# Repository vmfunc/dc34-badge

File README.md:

# dc34 badge

my findings and custom stuff for the def con 34 badge.

it's a **baochip-1x**, bunnie's mostly-open 22nm soc. vexriscv rv32imac + mmu at 350mhz,
quad picorv32 "bio" coprocessor at 700mhz, 2mib ecc sram, 4mib rram, usb 2.0 hs, running
xous. enumerates as `1d50:6198` "baosec-lite".

first dc badge whose rtl you can actually read, which changes the job. reversing something
you could have read is self-inflicted here.

## the ctf

flag 1 is stated outright in `bao1x-api/src/offsets/baosec.rs:151`:

```rust
/// A test value placed by FT into the memory array. If you can read the original value,
/// you've captured a flag!
/// There is a second flag stored somewhere else. Can you find it?
pub const THE_FLAG_1: SlotIndex = SlotIndex::Data(260, PartitionAccess::Fw0, RwPerms::ReadWrite);
```

32 bytes at `0x603E_2080`, burned at final test, `Fw0` so only boot1 and the keystore touch
it. not derived from anything, so it can't be computed. only read.

and it's in `KEY_SLOTS`, the set boot1 wipes on entry to developer mode. `sigcheck.rs:735`
runs `erase_secrets()` *before* unsigned code executes, so the erase is a precondition of
running your own image, not a consequence. no window, no ordering trick. flashing the badge
isn't a risk to the flag, it's the destruction of it.

that's the whole design, and it's a good one.

## every software path, and what killed it

measured on hardware, not inferred.

| path | why it's dead |
| --- | --- |
| bio bdma read | whitelist entirely empty. a filtered read gets redirected to `gutter` (resets to 0), nothing answers there, the core hangs. the hang is the oracle |
| boot1 `peek` | refuses `0x603D_A000`..`0x6040_0000` by address, *and* it's behind `unsafe-debug` and not in the shipped build |
| boot1 `uf2` | write path, bounded below `0x603D_A000`, can't address the flag, and unsigned use triggers the erase anyway |
| `image` verb | bounded 2048-byte framebuffer, 32 chunks, sequence enforced. the u16 index is not an oob write |
| ctaphid | init-only stub. init allocates channels and advertises caps `0x05`, then ping/wink/msg/cbor all return nothing |
| jtag | fused off, checked against `secboot.rs`'s hardcoded ifr reference at `0x6040_0180` |
| sign our own image | only `bao1`/`bao2`/`beta` avoid the erase, none of those private keys are public |

bio code execution *does* work. `bio` is an undocumented console verb that turns out to be
`baochip/bio-loader`'s protocol. proved it by loading a program that pushes `0x0BADF00D`,
then one that pops-adds-one-pushes, and reading back `badf00e`. it just can't reach memory.

so flag 1 is physical, and bunnie says so himself in the comment right above it: the
nuisance keys exist "to annoy microscopists trying to read the secret key by directly
imaging the rram array", and he concedes any readout above 97% accuracy gets repaired by
ecc. he named the attack, the tool and the pass mark. it's an iris job.

i gave up flag 1 on this badge on purpose, no microscope on hand, and flashed my own
firmware instead. slot 260 is erased here. for an unflashed badge the answer is still iris.

## the bug worth reporting

`rrc.sv:392-395` derives the acram index differently on its two paths. writes use
`{haddr[13:5], acram_idx}`, granular to 32 bytes. reads use `haddr[16:6]`, granular to 64.
a data slot is 32 bytes, so the read path drops the bit separating a slot from its
neighbour and the acl read index collapses to `slot >> 1`.

| pair | slots | access |
| --- | --- | --- |
| 130 | `THE_FLAG_1` (260) / `COLLATERAL[0]` (261) | fw0 / fw0 |
| **132** | **`COLLATERAL[3]` (264) / `BOOT1_PK_RECEIPT_SLOT0` (265)** | **fw0 / open** |

pair 132 straddles a privilege boundary. if the permissive side wins, slot 264 is readable
from a context that should never see it. arithmetic, checkable, worth telling baochip
regardless of the ctf. details in [notes/acl-aliasing.md](notes/acl-aliasing.md).

also a plain overflow in `test hue`: `base + 32` on a `u8` wraps, so asking for deep magenta
silently hands you green. fixed in my build.

## flag 2

still open, and it's the interesting one. from `vendor/dc34-vault/README.md`: light patterns
are traded between badges by qr and encrypted with a key **shared across the entire
population**. extract it and you're a seeder for arbitrary patterns. no microscope needed.
ranked leads and kill tests in [notes/leads.md](notes/leads.md).

## my firmware

reproduces bunnie's build, `loader.uf2` and `swap.uf2` byte-identical in size to the
official release, `xous.uf2` bigger by exactly what i added. deviations:

- `dc34-console` with `--features qa-test --features misc-test`. there are five feature
  gates in `cmds/test.rs`, not one, and `hue` is behind the second. `misc-test` carries
  `hue`/`autogamy`/`qrshow`/`qrget`/`cam`/`accel`/`adc`, `qa-test` carries
  `rate`/`transmute`/`bt`/`mate`. left `owc-test` and `wfi-stress-test` off, the first
  spends finite one-way counters and the second can hang the badge
- idle screen is mine: pfp, `vmfunc`, `it/its`. dc logo gone. regenerate with
  `tools/make_badge_art.py`
- strip reads `ud2.rip`
- boots lavender and breathing, nothing to type
- `test hue <val> [width]`, width 0 for one flat colour

on the breathing: the bio renderer computes brightness as
`cos(cd_period * 2pi * i/(count-1) +/- indextime/tau(cd_rate) * 2pi)`. `cd_period = 0` puts
every led in phase so the strip rises and falls together. `cd_rate` maps 0..255 onto tau
60..700, high is slow. that's the whole effect, no new code.

the default uses `force()` instead of setting the gene, so the heritable gene survives and
qr trading still works. it holds through repaints until you run `test hue`, trade, or breed,
then hands over for good.

## layout

```
notes/          the thinking. 00-log is the spine, leads.md is the hypothesis queue
firmware/       dumps/ is the vendor's signed release, built/ is mine, MANIFEST.md hashes both
vendor/         the six official bunnie repos, pinned, with provenance
tools/          host side, all of it safe to run half asleep
re/             ghidra scripts, bio programs, strings
art/            the ud2 wordmark and the generated badge card
captures/       gitignored. big, and worth exactly as much as the notes taken off them
solves/         one dir per challenge
docs/           the writeup
```

images get committed, captures don't. a firmware image is small evidence worth having in
history so a later diff can prove what changed. a logic capture is hundreds of mb of
observation. no git-lfs, it wants a network round trip and the whole premise is the network
won't be there.

## toolchain

```
nix develop
```

pinned flake, evaluates on x86_64-linux and aarch64-darwin. rv32 cross toolchain, ghidra,
radare2, binwalk, openocd, probe-rs, picotool, esptool, picocom, sigrok, rtl-sdr, hackrf,
python with pwntools/capstone/keystone/unicorn. rf gui tools are linux-only in nixpkgs and
gated accordingly.

pre-warm before you lose network:

```
nix develop --profile ./.dc34-profile -c true
```

## tools

```
./tools/console.py "help" "ver"                   talk to the console, refuses the fatal verbs
./tools/bio_upload.py --asm re/scripts/x.S        assemble + upload a bio program
./tools/sweep.py --range 0x603E0000 0x603F0000    map what bio may read
./tools/oled.py --ascii art/ud2.txt               picture onto the panel
./tools/leds.py --palette rose-pine               colours through the running lightgene
./tools/ctap.py info                              ctaphid
./tools/boot1.py                                  drive the bootloader, read-only
./tools/flash.sh firmware/built                   flash. makes you type FLASH
./tools/make_badge_art.py --pfp x.jpg             regenerate the idle screen
```

three things that cost me real time:

**console is 1000000 baud**, not 115200. wrong baud is indistinguishable from no console.

**pace writes inside the line.** console input goes through the keyboard service and its
buffer overflows on a fast full-length line, then takes the whole console silent. but
byte-at-a-time is worse: each tiny write becomes its own usb packet and the firmware
mis-samples it, so `ver` echoes back as `vrr`. corrupted input that still parses wastes far
more time than input that's loudly dropped. 24-byte pieces.

**`bio tx` is not a host-to-core path.** it feeds the queue the core pushes *to*, so anything
you send comes straight back on `bio rx` without a core ever seeing it. bake what a program
needs into the program. and a value pushed once gets eaten by the badge's own lightgenes
loop, so only continuous pushing survives.

## building the firmware

needs `xous-core` as a **sibling** dir, on **`dev`**, not the rev `dc34-console` pins.
`dc34-console` wants `keystore/owc-inc` which only exists on dev. tag the checkout or the
signer dies with `SemVer::from_git: no major version`.

```
cargo xtask install-toolkit          # prebuilt riscv32imac-unknown-xous std, no build-std
cargo xtask baosec-lite \
  ../dc34-console/target/riscv32imac-unknown-xous-elf/release/dc34-console~flash \
  ../dc34-vault/target/riscv32imac-unknown-xous-elf/release/dc34-vault \
  --no-timestamp --feature usb --kernel-feature debug-proc --no-verify
```

cratespec syntax matters: bare name is a workspace crate, `name^ver` is crates.io,
`name#url` is prebuilt, anything with a `/` is a prebuilt elf on disk, and
`name~swap|flash|ram` pins the region. out-of-tree apps go in as built binaries without
joining the xous workspace.

flash: hold `PROG` while plugging in, `./tools/flash.sh <dir>`, press `PROG` again.
back to stock: `./tools/flash.sh firmware/dumps/dc34-badge-latest`.

## links

- badge: https://defcon.org/34b/
- bunnie on the soc: https://www.bunniestudios.com/blog/2026/baochip-1x-a-mostly-open-22nm-soc-for-high-assurance-applications/
- sources: https://github.com/bunnie (dc34-console, dc34-vault, dc34-api, dc34-image, dc34-bio)
- rtl: https://github.com/baochip/baochip-1x
- xous: https://github.com/betrusted-io/xous-core
- iris: https://bunnie.org/iris

---

not affiliated with the badge designers. `vendor/` is their code, vendored with provenance in
`vendor/README.md`. `dc34-console`, `dc34-vault` and `dc34-api` ship no licence file, so
that's public-but-unlicensed, worth an email to `dc34@baochip.com` before anyone builds on
this.

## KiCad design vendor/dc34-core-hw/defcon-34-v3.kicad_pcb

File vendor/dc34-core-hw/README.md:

# DEFCON 34 Core Module Hardware Files

This contains the KiCAD files for the core module hardware design.

See [defcon's support page](https://defcon.org/34b) for more details.

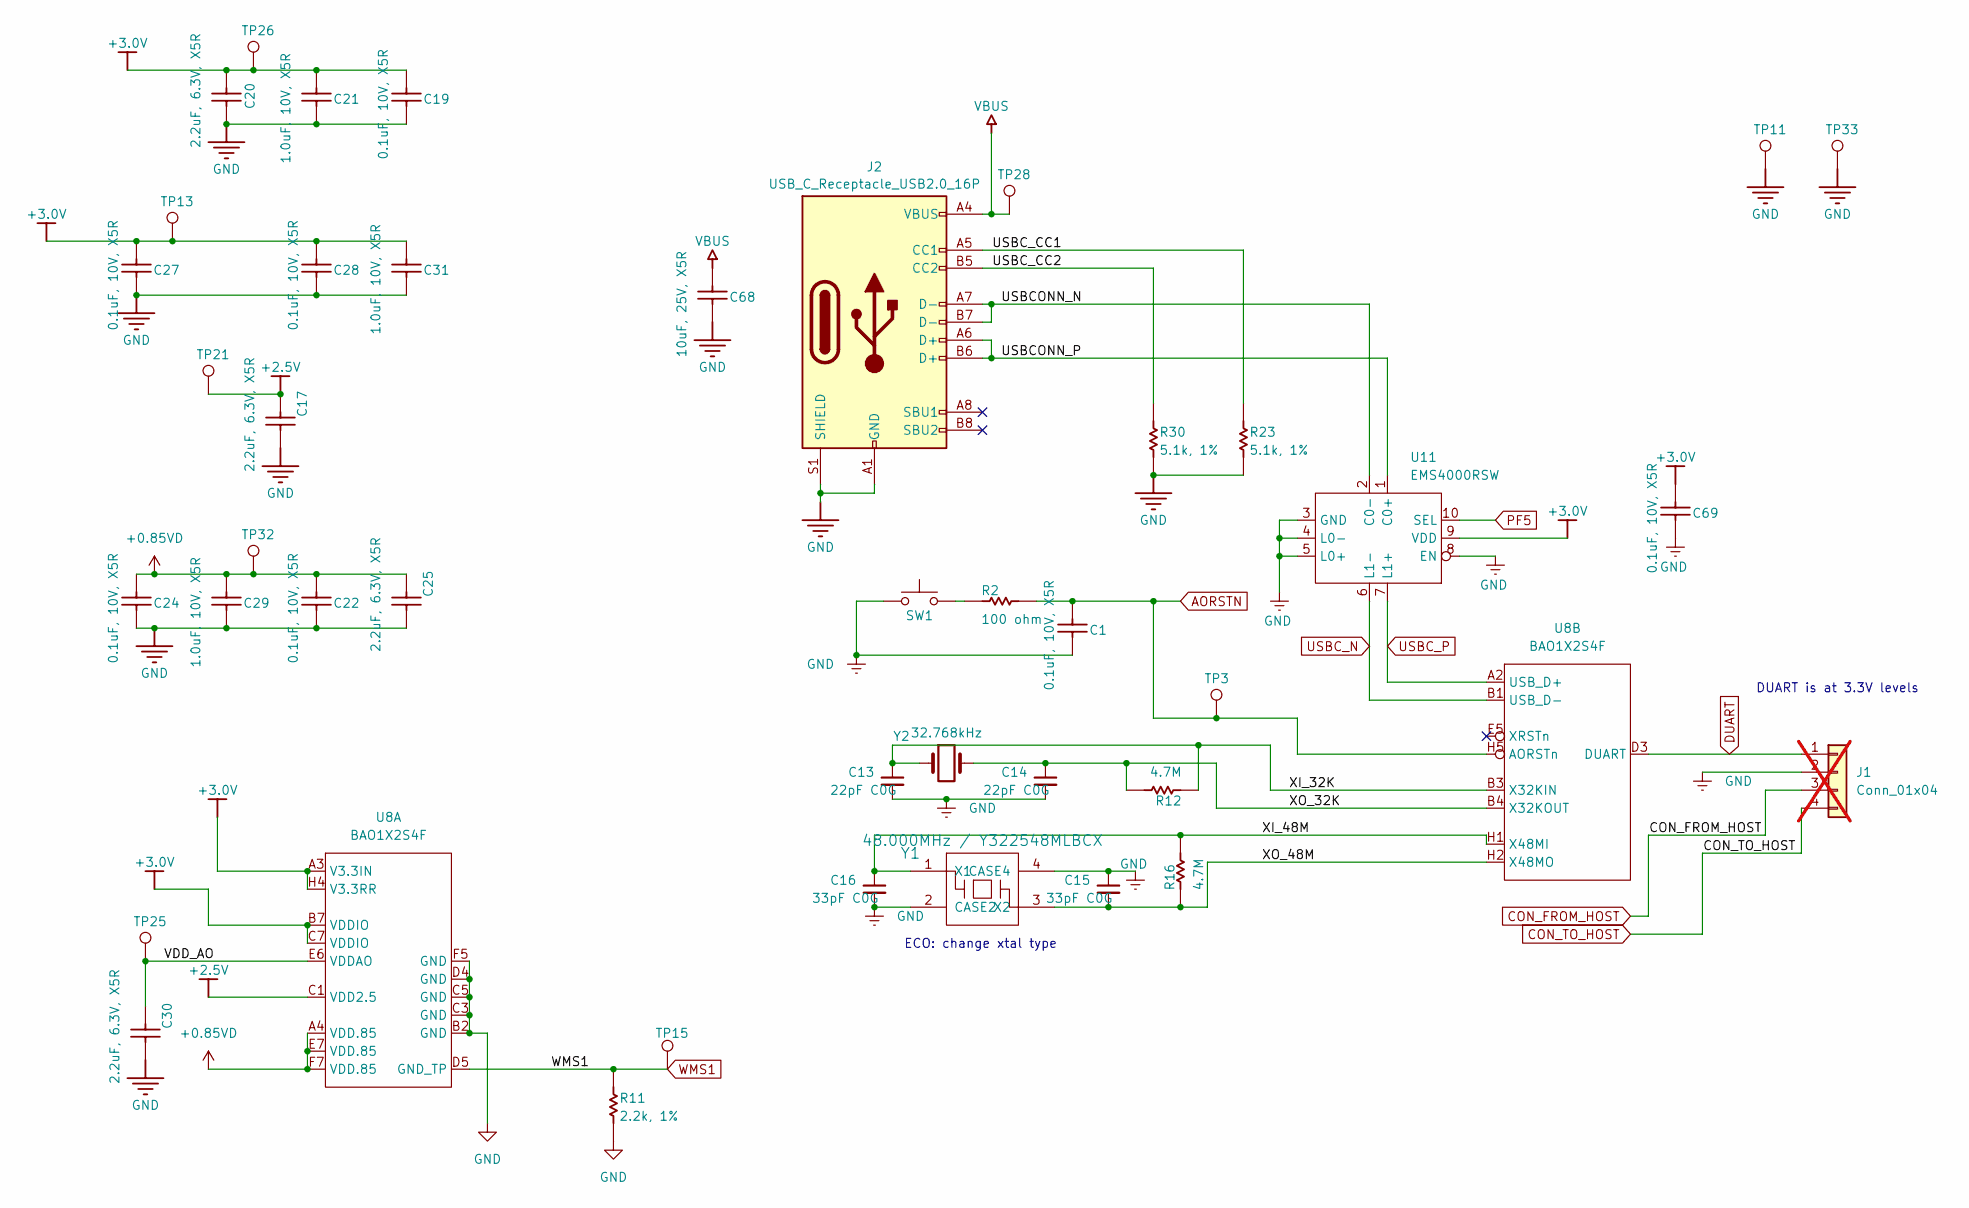
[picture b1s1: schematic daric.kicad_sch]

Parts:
C1, C19, C22, C24, C27, C28, C69: 0.1uF, 10V, X5R; C_0201_0603Metric; MPN CL05B104KO5NNNC; LCSC C76934
C13, C14: 22pF C0G; C_0201_0603Metric; Rating C0G 50V 0201; MPN ANY; LCSC C57783
C15, C16: 33pF C0G; C_0201_0603Metric; Rating C0G 50V 0201; MPN ANY; LCSC C56903
C17, C20, C25, C30: 2.2uF, 6.3V, X5R; C_0201_0603Metric; MPN GRM033R60J225ME47D; LCSC C76933
C21, C29, C31: 1.0uF, 10V, X5R; C_0201_0603Metric; MPN CL05A105KA5NQNC; LCSC C76935
C68: 10uF, 25V, X5R; C_0603_1608Metric; MPN CL10A106MA8NRNC; LCSC C96446
J1: Conn_01x04; PinHeader_1x04_P2.54mm_Vertical; not fitted
J2: USB_C_Receptacle_USB2.0_16P; USB_C_Receptacle_HRO_TYPE-C-31-M-12; LCSC C165948
R2: 100 ohm; R_0402_1005Metric; MPN ANY; LCSC C106232
R11: 2.2k, 1%; R_0402_1005Metric; MPN ANY; LCSC C114762
R12, R16: 4.7M; R_0402_1005Metric; MPN ANY; LCSC C474132
R23, R30: 5.1k, 1%; R_0402_1005Metric; MPN ANY; LCSC C25905
SW1: SW_Push; TS24CA; MPN TS24CA; LCSC C393942
TP3, TP11, TP13, TP15, TP21, TP25, TP26, TP28, TP32, TP33: TestPoint; TestPoint_Pad_D1.2mm
U8: BAO1X2S4F; WLCSP-71_9x8_4.062x3.762mm
U11: EMS4000RSW; QFN-10_1.4x1.8_Pitch0.4mm; LCSC C49186227
Y1: 48.000MHz / Y322548MLBCX; Crystal_SMD_3225-4Pin_3.2x2.5mm; LCSC C49158137
Y2: 32.768kHz; Crystal_SMD_TXC_9HT11-2Pin_2.0x1.2mm; LCSC C55208

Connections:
+0.85VD: C22.1, C24.1, C25.1, C29.1, TP32.1, U8.A4 (VDD.85), U8.E7 (VDD.85), U8.F7 (VDD.85); also elsewhere on the board
+2.5V: C17.1, TP21.1, U8.C1 (VDD2.5)
+3.0V: C19.1, C20.1, C21.1, C27.1, C28.1, C31.1, C69.1, TP13.1, TP26.1, U8.A3 (V3.3IN), U8.B7 (VDDIO), U8.C7 (VDDIO), U8.H4 (V3.3RR), U11.9 (VDD); also elsewhere on the board
/Daric/USBCONN_N: J2.A7 (D-), J2.B7 (D-), U11.2 (C0-)
/Daric/USBCONN_P: J2.A6 (D+), J2.B6 (D+), U11.1 (C0+)
/Daric/USBC_CC1: J2.A5 (CC1), R23.2
/Daric/USBC_CC2: J2.B5 (CC2), R30.2
/Daric/VDD_AO: C30.1, TP25.1, U8.E6 (VDDAO)
/Daric/XI_32K: C13.1, R12.1, U8.B3 (X32KIN), Y2.1
/Daric/XI_48M: C16.1, R16.2, U8.H1 (X48MI), Y1.1 (X1)
/Daric/XO_32K: C14.1, R12.2, U8.B4 (X32KOUT), Y2.2
/Daric/XO_48M: C15.2, R16.1, U8.H2 (X48MO), Y1.3 (X2)
AORSTN: C1.1, R2.2, TP3.1, U8.H5 (AORSTn); also elsewhere on the board
CON_FROM_HOST: J1.3; also elsewhere on the board
CON_TO_HOST: J1.4; also elsewhere on the board
DUART: J1.1, U8.D3 (DUART); also elsewhere on the board
GND: C1.2, C13.2, C14.2, C15.1, C16.2, C17.2, C19.2, C20.2, C21.2, C22.2, C24.2, C25.2, C27.2, C28.2, C29.2, C30.2, C31.2, C68.2, C69.2, J1.2, J2.A1 (GND), J2.A12 (GND), J2.B1 (GND), J2.B12 (GND), J2.S1 (SHIELD), R11.2, R23.1, R30.1, SW1.1, TP11.1, TP33.1, U8.B2 (GND), U8.C3 (GND), U8.C5 (GND), U8.D4 (GND), U8.F5 (GND), U11.3 (GND), U11.4 (L0-), U11.5 (L0+), U11.8 (EN), Y1.2 (CASE2), Y1.4 (CASE4); also elsewhere on the board
unnamed: R2.1, SW1.2
PF5: U11.10 (SEL); also elsewhere on the board
USBC_N: U8.B1 (USB_D-), U11.6 (L1-)
USBC_P: U8.A2 (USB_D+), U11.7 (L1+)
VBUS: C68.1, J2.A4 (VBUS), J2.A9 (VBUS), J2.B4 (VBUS), J2.B9 (VBUS), TP28.1; also elsewhere on the board
WMS1: R11.1, TP15.1, U8.D5 (GND_TP); also elsewhere on the board

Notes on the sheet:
ECO: change xtal type
DUART is at 3.3V levels

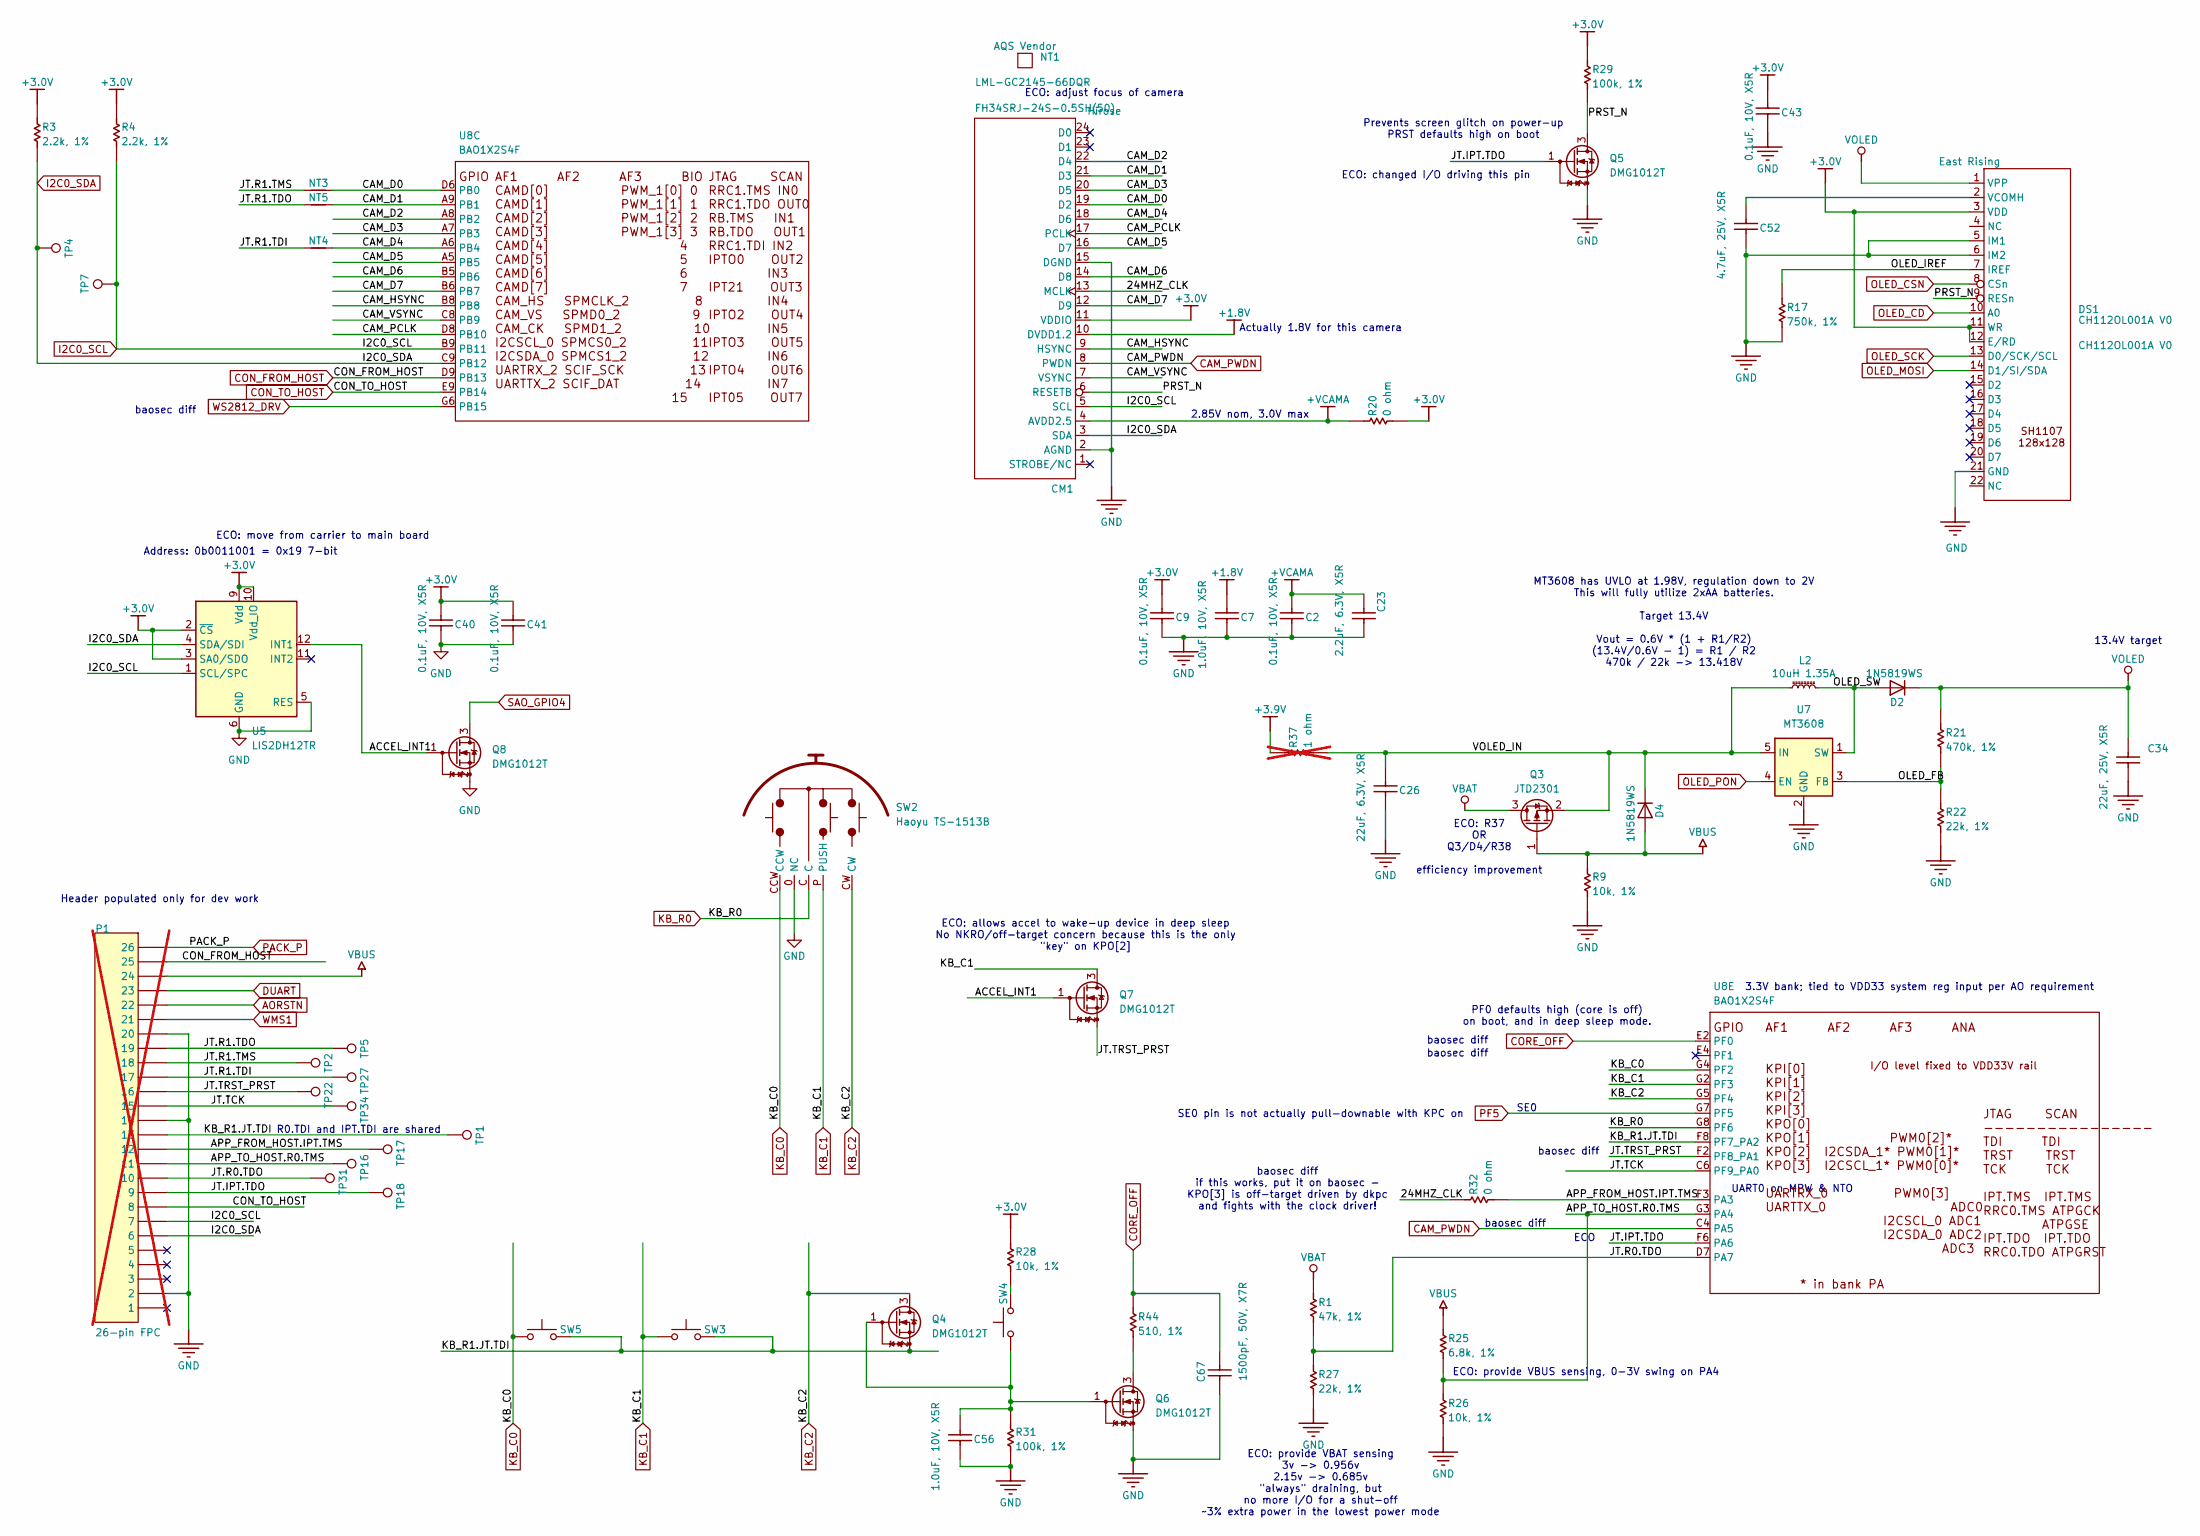
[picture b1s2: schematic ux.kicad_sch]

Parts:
C2, C9, C40, C41, C43: 0.1uF, 10V, X5R; C_0201_0603Metric; MPN CL05B104KO5NNNC; LCSC C76934
C7, C56: 1.0uF, 10V, X5R; C_0201_0603Metric; MPN CL05A105KA5NQNC; LCSC C76935
C23: 2.2uF, 6.3V, X5R; C_0201_0603Metric; MPN GRM033R60J225ME47D; LCSC C76933
C26: 22uF, 6.3V, X5R; C_0603_1608Metric; MPN CL10A226MQ8NRNC; LCSC C59461
C34: 22uF, 25V, X5R; C_0805_2012Metric; LCSC C7419435
C52: 4.7uF, 25V, X5R; C_0805_2012Metric; MPN CL21A475KAQNNNE; LCSC C1779
C67: 1500pF, 50V, X7R; C_0402_1005Metric; MPN CC0402KRX7R9BB152; LCSC C107022
CM1: HRS_FH34SRJ-24S-0.5SH(50); MPN FH34SRJ-24S-0.5SH(50); LCSC C324726
D2, D4: 1N5819WS; D_SOD-323-B; MPN SD103AWS; LCSC C191023
DS1: CH112OL001A V0; ER-OLED-1.12_BACKSIDE-1.5mm-offset; MPN CH112OL001A V0
L2: 10uH 1.35A; L_APV_ANR252012; MPN FHD252012S-100MT; LCSC C602018
NT1: LML-GC2145-66DQR; GC2145-lens-up; PARTNUMBER LML-GC2145-66DQR
NT3, NT4, NT5: NetTie_2; NetTie-2_SMD_Pad0.5mm
P1: 26-pin FPC; HRS_FH34SRJ-26S-0.5SH(50); MPN FH34SRJ-26S-0.5SH(99); LCSC C596726; not fitted
Q3: JTD2301; SOT-23; LCSC C42443454
Q4, Q5, Q6, Q7, Q8: DMG1012T; SOT-523-B; LCSC C20512
R1: 47k, 1%; R_0201_0603Metric; MPN ANY; LCSC C138139
R3, R4: 2.2k, 1%; R_0402_1005Metric; MPN ANY; LCSC C114762
R9, R26, R28: 10k, 1%; R_0201_0603Metric; MPN ANY; LCSC C106225
R17: 750k, 1%; R_0402_1005Metric; MPN ANY; LCSC C2909381
R20, R32: 0 ohm; R_0402_1005Metric; MPN ANY; LCSC C17168
R21: 470k, 1%; R_0402_1005Metric; MPN ANY; LCSC C25790
R22, R27: 22k, 1%; R_0201_0603Metric; MPN ANY; LCSC C474416
R25: 6.8k, 1%; R_0201_0603Metric; MPN ANY; LCSC C274877
R29, R31: 100k, 1%; R_0201_0603Metric; MPN ANY; LCSC C106224
R37: 1 ohm; R_0402_1005Metric; MPN ANY; LCSC C185446; not fitted
R44: 510, 1%; R_0201_0603Metric; MPN ANY; LCSC C965358
SW2: Haoyu TS-1513B; TS-1513B; LCSC C318951
SW3, SW4, SW5: SW_Push; SW_Push_1P1T_XKB_TS-1187A; MPN TS-1187A-B-B-B; LCSC C528026
TP1, TP2, TP4, TP5, TP7, TP16, TP17, TP18, TP22, TP27, TP31, TP34: TestPoint; TestPoint_Pad_D1.2mm
U5: LIS2DH12TR; LGA-12_2x2mm_P0.5mm; LCSC C110926
U7: MT3608; SOT-23-6; LCSC C84817
U8: BAO1X2S4F; WLCSP-71_9x8_4.062x3.762mm

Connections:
+1.8V: C7.1, CM1.10 (DVDD1.2); also elsewhere on the board
+3.0V: C9.1, C40.1, C41.1, C43.1, CM1.11 (VDDIO), DS1.3 (VDD), DS1.11 (WR), DS1.12 (E/RD), R3.1, R4.1, R20.2, R28.1, R29.1, U5.2 (~CS), U5.3 (SA0/SDO), U5.9 (Vdd), U5.10 (Vdd_IO); also elsewhere on the board
+3.9V: R37.1; also elsewhere on the board
+VCAMA: C2.1, C23.1, CM1.4 (AVDD2.5), R20.1
/ux/24MHZ_CLK: CM1.13 (MCLK), R32.1
/ux/ACCEL_INT1: Q7.1 (G), Q8.1 (G), U5.12 (INT1)
/ux/APP_FROM_HOST.IPT.TMS: P1.12, R32.2, TP17.1, U8.F3 (PA3)
/ux/APP_TO_HOST.R0.TMS: P1.11, R25.2, R26.1, TP16.1, U8.G3 (PA4)
/ux/CAM_D0: CM1.19 (D2), NT3.2, U8.D6 (PB0)
/ux/CAM_D1: CM1.21 (D3), NT5.2, U8.A9 (PB1)
/ux/CAM_D2: CM1.22 (D4), U8.A8 (PB2)
/ux/CAM_D3: CM1.20 (D5), U8.A7 (PB3)
/ux/CAM_D4: CM1.18 (D6), NT4.2, U8.A6 (PB4)
/ux/CAM_D5: CM1.16 (D7), U8.A5 (PB5)
/ux/CAM_D6: CM1.14 (D8), U8.B5 (PB6)
/ux/CAM_D7: CM1.12 (D9), U8.B6 (PB7)
/ux/CAM_HSYNC: CM1.9 (HSYNC), U8.B8
/ux/CAM_PCLK: CM1.17 (PCLK), U8.D8 (PB10)
/ux/CAM_VSYNC: CM1.7 (VSYNC), U8.C8 (PB9)
/ux/JT.IPT.TDO: P1.9, Q5.1 (G), TP18.1, U8.F6 (PA6)
/ux/JT.R0.TDO: P1.10, R1.2, R27.1, TP31.1, U8.D7 (PA7)
/ux/JT.R1.TDI: NT4.1, P1.17, TP27.1
/ux/JT.R1.TDO: NT5.1, P1.19, TP5.1
/ux/JT.R1.TMS: NT3.1, P1.18, TP2.1
/ux/JT.TCK: P1.15, TP34.1, U8.C6 (PF9_PA0)
/ux/JT.TRST_PRST: P1.16, Q7.2 (S), TP22.1, U8.F2 (PF8_PA1)
/ux/KB_R1.JT.TDI: P1.13, Q4.2 (S), SW3.2, SW5.2, TP1.1, U8.F8 (PF7_PA2)
/ux/OLED_FB: R21.2, R22.1, U7.3 (FB)
/ux/OLED_IREF: DS1.7 (IREF), R17.1
/ux/OLED_SW: D2.2 (A), L2.2, U7.1 (SW)
/ux/PRST_N: CM1.6 (RESETB), DS1.9 (RESn), Q5.3 (D), R29.2
/ux/VOLED_IN: C26.1, D4.1 (K), L2.1, Q3.2 (S), R37.2, U7.5 (IN)
AORSTN: P1.22; also elsewhere on the board
CAM_PWDN: CM1.8 (PWDN), U8.C4 (PA5)
CON_FROM_HOST: P1.25, U8.D9 (PB13); also elsewhere on the board
CON_TO_HOST: P1.8, U8.E9 (PB14); also elsewhere on the board
CORE_OFF: C67.2, R44.1, U8.E2 (PF0); also elsewhere on the board
DUART: P1.23; also elsewhere on the board
GND: C2.2, C7.2, C9.2, C23.2, C26.2, C34.2, C40.2, C41.2, C43.2, C52.2, C56.2, C67.1, CM1.2 (AGND), CM1.15 (DGND), DS1.5 (IM1), DS1.6 (IM2), DS1.21 (GND), P1.2, P1.14, P1.20, Q5.2 (S), Q6.2 (S), Q8.2 (S), R9.2, R17.2, R22.2, R26.2, R27.2, R31.2, SW2.0 (NC), U5.5 (RES), U5.6 (GND), U5.7 (GND), U5.8 (GND), U7.2 (GND); also elsewhere on the board
I2C0_SCL: CM1.5 (SCL), P1.7, R4.2, TP7.1, U5.1 (SCL/SPC), U8.B9 (PB11); also elsewhere on the board
I2C0_SDA: CM1.3 (SDA), P1.6, R3.2, TP4.1, U5.4 (SDA/SDI), U8.C9 (PB12); also elsewhere on the board
KB_C0: SW2.CCW, SW5.1, U8.G4 (PF2)
KB_C1: Q7.3 (D), SW2.P (PUSH), SW3.1, U8.G2 (PF3)
KB_C2: Q4.3 (D), SW2.CW, U8.G5 (PF4)
KB_R0: SW2.C, U8.G8 (PF6)
unnamed: C52.1, DS1.2 (VCOMH)
unnamed: C56.1, Q4.1 (G), Q6.1 (G), R31.1, SW4.1
unnamed: Q6.3 (D), R44.2
unnamed: R28.2, SW4.2
OLED_CD: DS1.10 (A0); also elsewhere on the board
OLED_CSN: DS1.8 (CSn); also elsewhere on the board
OLED_MOSI: DS1.14 (D1/SI/SDA); also elsewhere on the board
OLED_PON: U7.4 (EN); also elsewhere on the board
OLED_SCK: DS1.13 (D0/SCK/SCL); also elsewhere on the board
PACK_P: P1.26; also elsewhere on the board
PF5: U8.G7 (PF5); also elsewhere on the board
SAO_GPIO4: Q8.3 (D); also elsewhere on the board
VBAT: Q3.3 (D), R1.1; also elsewhere on the board
VBUS: D4.2 (A), P1.24, Q3.1 (G), R9.1, R25.1; also elsewhere on the board
VOLED: C34.1, D2.1 (K), DS1.1 (VPP), R21.1
WMS1: P1.21; also elsewhere on the board
WS2812_DRV: U8.G6 (PB15); also elsewhere on the board

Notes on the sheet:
Prevents screen glitch on power-up PRST defaults high on boot
Header populated only for dev work
ECO: changed I/O driving this pin
3.3V bank; tied to VDD33 system reg input per AO requirement
PF0 defaults high (core is off) on boot, and in deep sleep mode.
SE0 pin is not actually pull-downable with KPC on
SE0
ECO
ECO: provide VBUS sensing, 0-3V swing on PA4
baosec diff
UART0 on MPW & NTO
baosec diff if this works, put it on baosec - KPO[3] is off-target driven by dkpc and fights with the clock driver!
Actually 1.8V for this camera
MT3608 has UVLO at 1.98V, regulation down to 2V This will fully utilize 2xAA batteries. Target 13.4V Vout = 0.6V * (1 + R1/R2) (13.4V/0.6V - 1) = R1 / R2 470k / 22k -> 13.418V
ECO: adjust focus of camera
13.4V target
ECO: move from carrier to main board
2.85V nom, 3.0V max
ECO: R37 OR Q3/D4/R38 efficiency improvement
ECO: provide VBAT sensing 3v -> 0.956v 2.15v -> 0.685v "always" draining, but no more I/O for a shut-off ~3% extra power in the lowest power mode
Address: 0b0011001 = 0x19 7-bit
R0.TDI and IPT.TDI are shared
ECO: allows accel to wake-up device in deep sleep No NKRO/off-target concern because this is the only "key" on KPO[2]

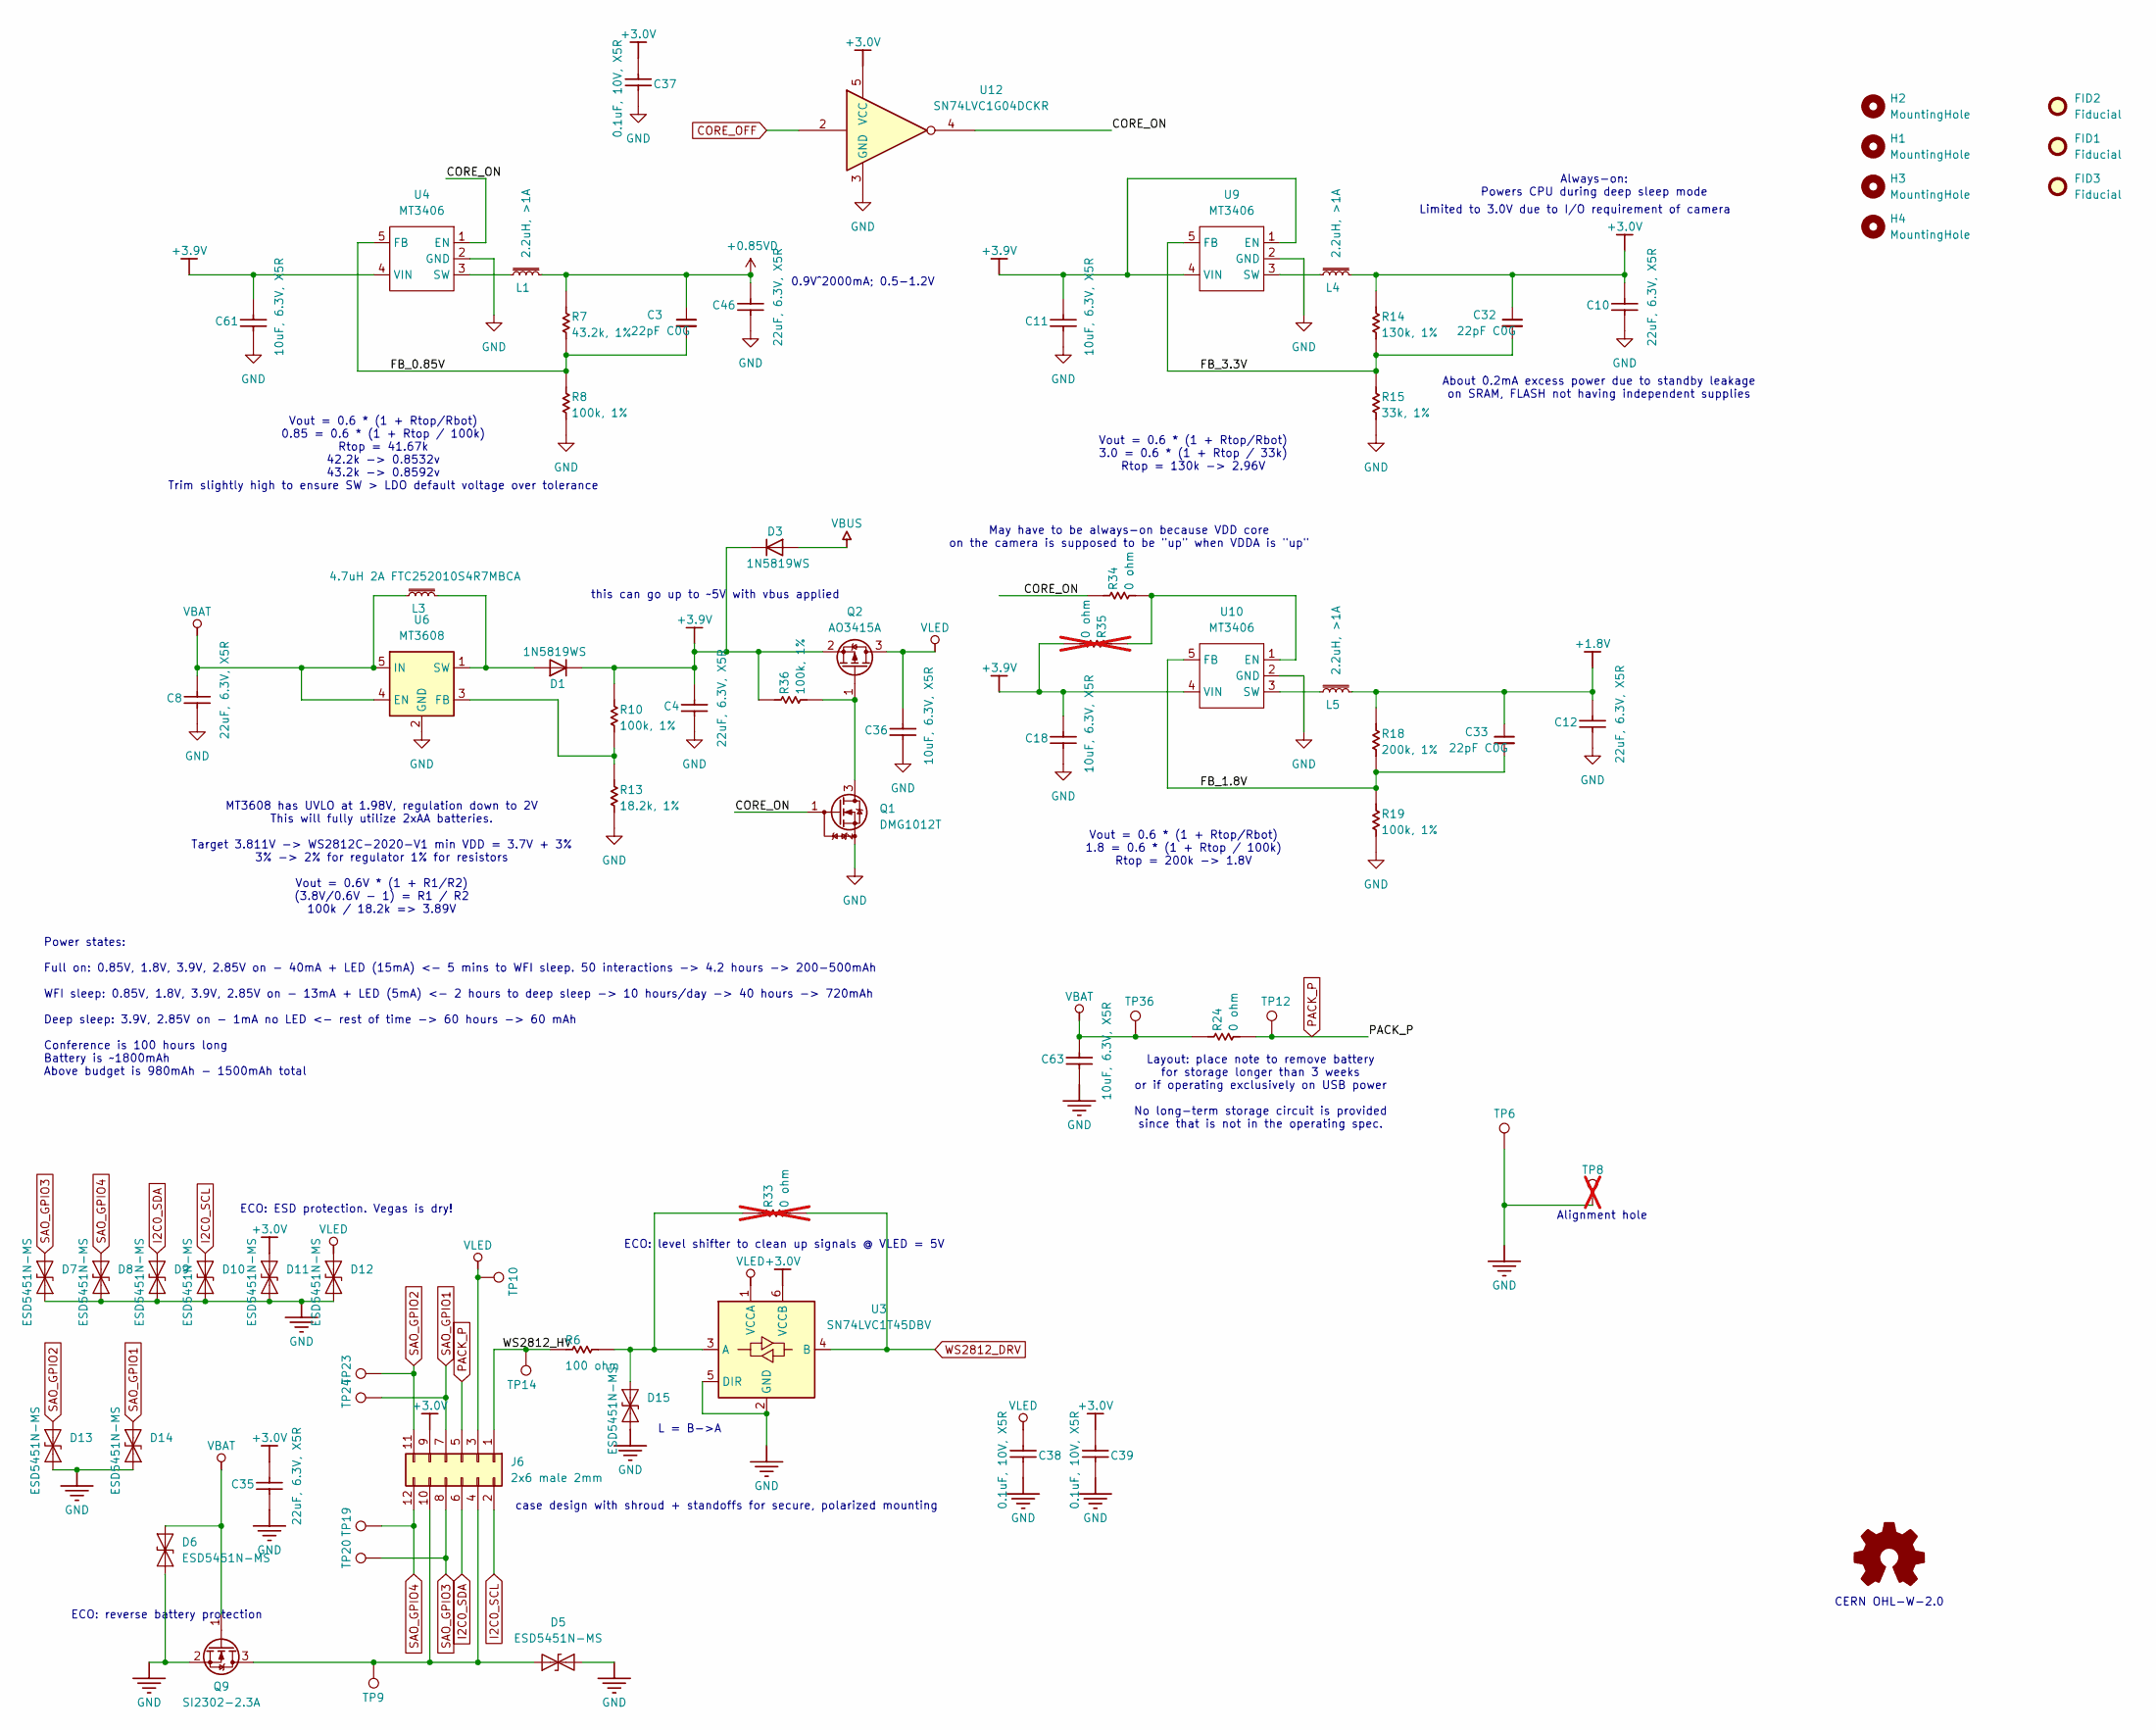
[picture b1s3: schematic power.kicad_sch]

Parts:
C3, C32, C33: 22pF C0G; C_0201_0603Metric; Rating C0G 50V 0201; MPN ANY; LCSC C57783
C4, C8, C10, C12, C35, C46: 22uF, 6.3V, X5R; C_0603_1608Metric; MPN CL10A226MQ8NRNC; LCSC C59461
C11, C18, C36, C61, C63: 10uF, 6.3V, X5R; C_0402_1005Metric; MPN CL05A106MQ5NUNC; LCSC C15525
C37, C38, C39: 0.1uF, 10V, X5R; C_0201_0603Metric; MPN CL05B104KO5NNNC; LCSC C76934
D1, D3: 1N5819WS; D_SOD-323-B; MPN SD103AWS; LCSC C191023
D5, D6, D7, D8, D9, D10, D11, D12, D13, D14, D15: ESD5451N-MS; D_SOD-882D; LCSC C2802295
FID1, FID2: Fiducial; IRIS fiducial 0.4mm
FID3: Fiducial; IRIS fiducial2 0.4mm
H1, H2, H3, H4: MountingHole; MountingHole_2.2mm_M2
J6: 2x6 male 2mm; PinHeader_2x06_P2.00mm_Vertical; LCSC C42385474
L1, L4, L5: 2.2uH, >1A; L_0805_2012Metric; LCSC C42455261
L3: 4.7uH 2A FTC252010S4R7MBCA; L_1008_2520Metric; LCSC C5832360
Q1: DMG1012T; SOT-523-B; LCSC C20512
Q2: AO3415A; SOT-23; LCSC C133233
Q9: SI2302-2.3A; SOT-23; LCSC C5296725
R6: 100 ohm; R_0402_1005Metric; MPN ANY; LCSC C106232
R7: 43.2k, 1%; R_0201_0603Metric; MPN ANY; LCSC C158519
R8, R10, R19, R36: 100k, 1%; R_0201_0603Metric; MPN ANY; LCSC C106224
R13: 18.2k, 1%; R_0201_0603Metric; MPN ANY; LCSC C320733
R14: 130k, 1%; R_0201_0603Metric; MPN ANY; LCSC C138176
R15: 33k, 1%; R_0201_0603Metric; MPN ANY; LCSC C320835
R18: 200k, 1%; R_0201_0603Metric; MPN ANY; LCSC C138163
R24, R34: 0 ohm; R_0402_1005Metric; MPN ANY; LCSC C17168
R33, R35: 0 ohm; R_0402_1005Metric; MPN ANY; LCSC C17168; not fitted
TP6, TP9, TP10, TP12, TP14, TP19, TP20, TP23, TP24, TP36: TestPoint; TestPoint_Pad_D1.2mm
TP8: TestPoint; PinHeader_1x01_P2.54mm_Vertical; not fitted
U3: SN74LVC1T45DBV; SOT-23-6; LCSC C168856
U4, U9, U10: MT3406; SOT-23-5; LCSC C22462728
U6: MT3608; SOT-23-6; LCSC C84817
U12: SN74LVC1G04DCKR; SOT-353_SC-70-5; LCSC C2983744

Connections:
+0.85VD: C3.1, C46.2, L1.2, R7.1; also elsewhere on the board
+1.8V: C12.2, C33.1, L5.2, R18.1; also elsewhere on the board
+3.0V: C10.2, C32.1, C35.2, C37.1, C39.1, D11.2 (A2), J6.9, L4.2, R14.1, U3.6 (VCCB), U12.5 (VCC); also elsewhere on the board
+3.9V: C4.2, C11.2, C18.2, C61.2, D1.1 (K), D3.1 (K), Q2.2 (S), R10.1, R35.2, R36.2, U4.4 (VIN), U9.1 (EN), U9.4 (VIN), U10.4 (VIN); also elsewhere on the board
/Power/CORE_ON: Q1.1 (G), R34.1, U4.1 (EN), U12.4
/Power/FB_0.85V: C3.2, R7.2, R8.1, U4.5 (FB)
/Power/FB_1.8V: C33.2, R18.2, R19.1, U10.5 (FB)
/Power/FB_3.3V: C32.2, R14.2, R15.1, U9.5 (FB)
/Power/WS2812_HV: J6.1, R6.1, TP14.1
CORE_OFF: U12.2; also elsewhere on the board
GND: C4.1, C8.1, C10.1, C11.1, C12.1, C18.1, C35.1, C36.1, C37.2, C38.2, C39.2, C46.1, C61.1, C63.1, D5.2 (A2), D6.1 (A1), D7.1 (A1), D8.1 (A1), D9.1 (A1), D10.1 (A1), D11.1 (A1), D12.1 (A1), D13.1 (A1), D14.1 (A1), D15.1 (A1), Q1.2 (S), Q9.2 (S), R8.2, R13.2, R15.2, R19.2, TP6.1, TP8.1, U3.2 (GND), U3.5 (DIR), U4.2 (GND), U6.2 (GND), U9.2 (GND), U10.2 (GND), U12.3 (GND); also elsewhere on the board
I2C0_SCL: D10.2 (A2), J6.2; also elsewhere on the board
I2C0_SDA: D9.2 (A2), J6.6; also elsewhere on the board
unnamed: D1.2 (A), L3.2, U6.1 (SW)
unnamed: D5.1 (A1), J6.4, J6.10, Q9.3 (D), TP9.1
unnamed: D15.2 (A2), R6.2, R33.1, U3.3 (A)
unnamed: Q1.3 (D), Q2.1 (G), R36.1
unnamed: L1.1, U4.3 (SW)
unnamed: R10.2, R13.1, U6.3 (FB)
unnamed: L4.1, U9.3 (SW)
unnamed: R34.2, R35.1, U10.1 (EN)
unnamed: L5.1, U10.3 (SW)
PACK_P: J6.5, R24.2, TP12.1; also elsewhere on the board
SAO_GPIO1: D14.2 (A2), J6.7, TP24.1; also elsewhere on the board
SAO_GPIO2: D13.2 (A2), J6.11, TP23.1; also elsewhere on the board
SAO_GPIO3: D7.2 (A2), J6.8, TP20.1; also elsewhere on the board
SAO_GPIO4: D8.2 (A2), J6.12, TP19.1; also elsewhere on the board
VBAT: C8.2, C63.2, D6.2 (A2), L3.1, Q9.1 (G), R24.1, TP36.1, U6.4 (EN), U6.5 (IN); also elsewhere on the board
VBUS: D3.2 (A); also elsewhere on the board
VLED: C36.2, C38.1, D12.2 (A2), J6.3, Q2.3 (D), TP10.1, U3.1 (VCCA)
WS2812_DRV: R33.2, U3.4 (B); also elsewhere on the board

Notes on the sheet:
L = B->A
MT3608 has UVLO at 1.98V, regulation down to 2V This will fully utilize 2xAA batteries. Target 3.811V -> WS2812C-2020-V1 min VDD = 3.7V + 3% 3% -> 2% for regulator 1% for resistors Vout = 0.6V * (1 + R1/R2) (3.8V/0.6V - 1) = R1 / R2 100k / 18.2k => 3.89V
Always-on: Powers CPU during deep sleep mode
Vout = 0.6 * (1 + Rtop/Rbot) 3.0 = 0.6 * (1 + Rtop / 33k) Rtop = 130k -> 2.96V
0.9V^2000mA; 0.5-1.2V
ECO: reverse battery protection
May have to be always-on because VDD core on the camera is supposed to be "up" when VDDA is "up"
About 0.2mA excess power due to standby leakage on SRAM, FLASH not having independent supplies
Layout: place note to remove battery for storage longer than 3 weeks or if operating exclusively on USB power No long-term storage circuit is provided since that is not in the operating spec.
case design with shroud + standoffs for secure, polarized mounting
this can go up to ~5V with vbus applied
Alignment hole
CERN OHL-W-2.0
Vout = 0.6 * (1 + Rtop/Rbot) 1.8 = 0.6 * (1 + Rtop / 100k) Rtop = 200k -> 1.8V
Vout = 0.6 * (1 + Rtop/Rbot) 0.85 = 0.6 * (1 + Rtop / 100k) Rtop = 41.67k 42.2k -> 0.8532v 43.2k -> 0.8592v Trim slightly high to ensure SW > LDO default voltage over tolerance
Power states: Full on: 0.85V, 1.8V, 3.9V, 2.85V on - 40mA + LED (15mA) <- 5 mins to WFI sleep. 50 interactions -> 4.2 hours -> 200-500mAh WFI sleep: 0.85V, 1.8V, 3.9V, 2.85V on - 13mA + LED (5mA) <- 2 hours to deep sleep -> 10 hours/day -> 40 hours -> 720mAh Deep sleep: 3.9V, 2.85V on - 1mA no LED 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
Limited to 3.0V due to I/O requirement of camera
ECO: ESD protection. Vegas is dry!
ECO: level shifter to clean up signals @ VLED = 5V
